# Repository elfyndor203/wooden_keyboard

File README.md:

# wooden_keyboard
My new keyboard

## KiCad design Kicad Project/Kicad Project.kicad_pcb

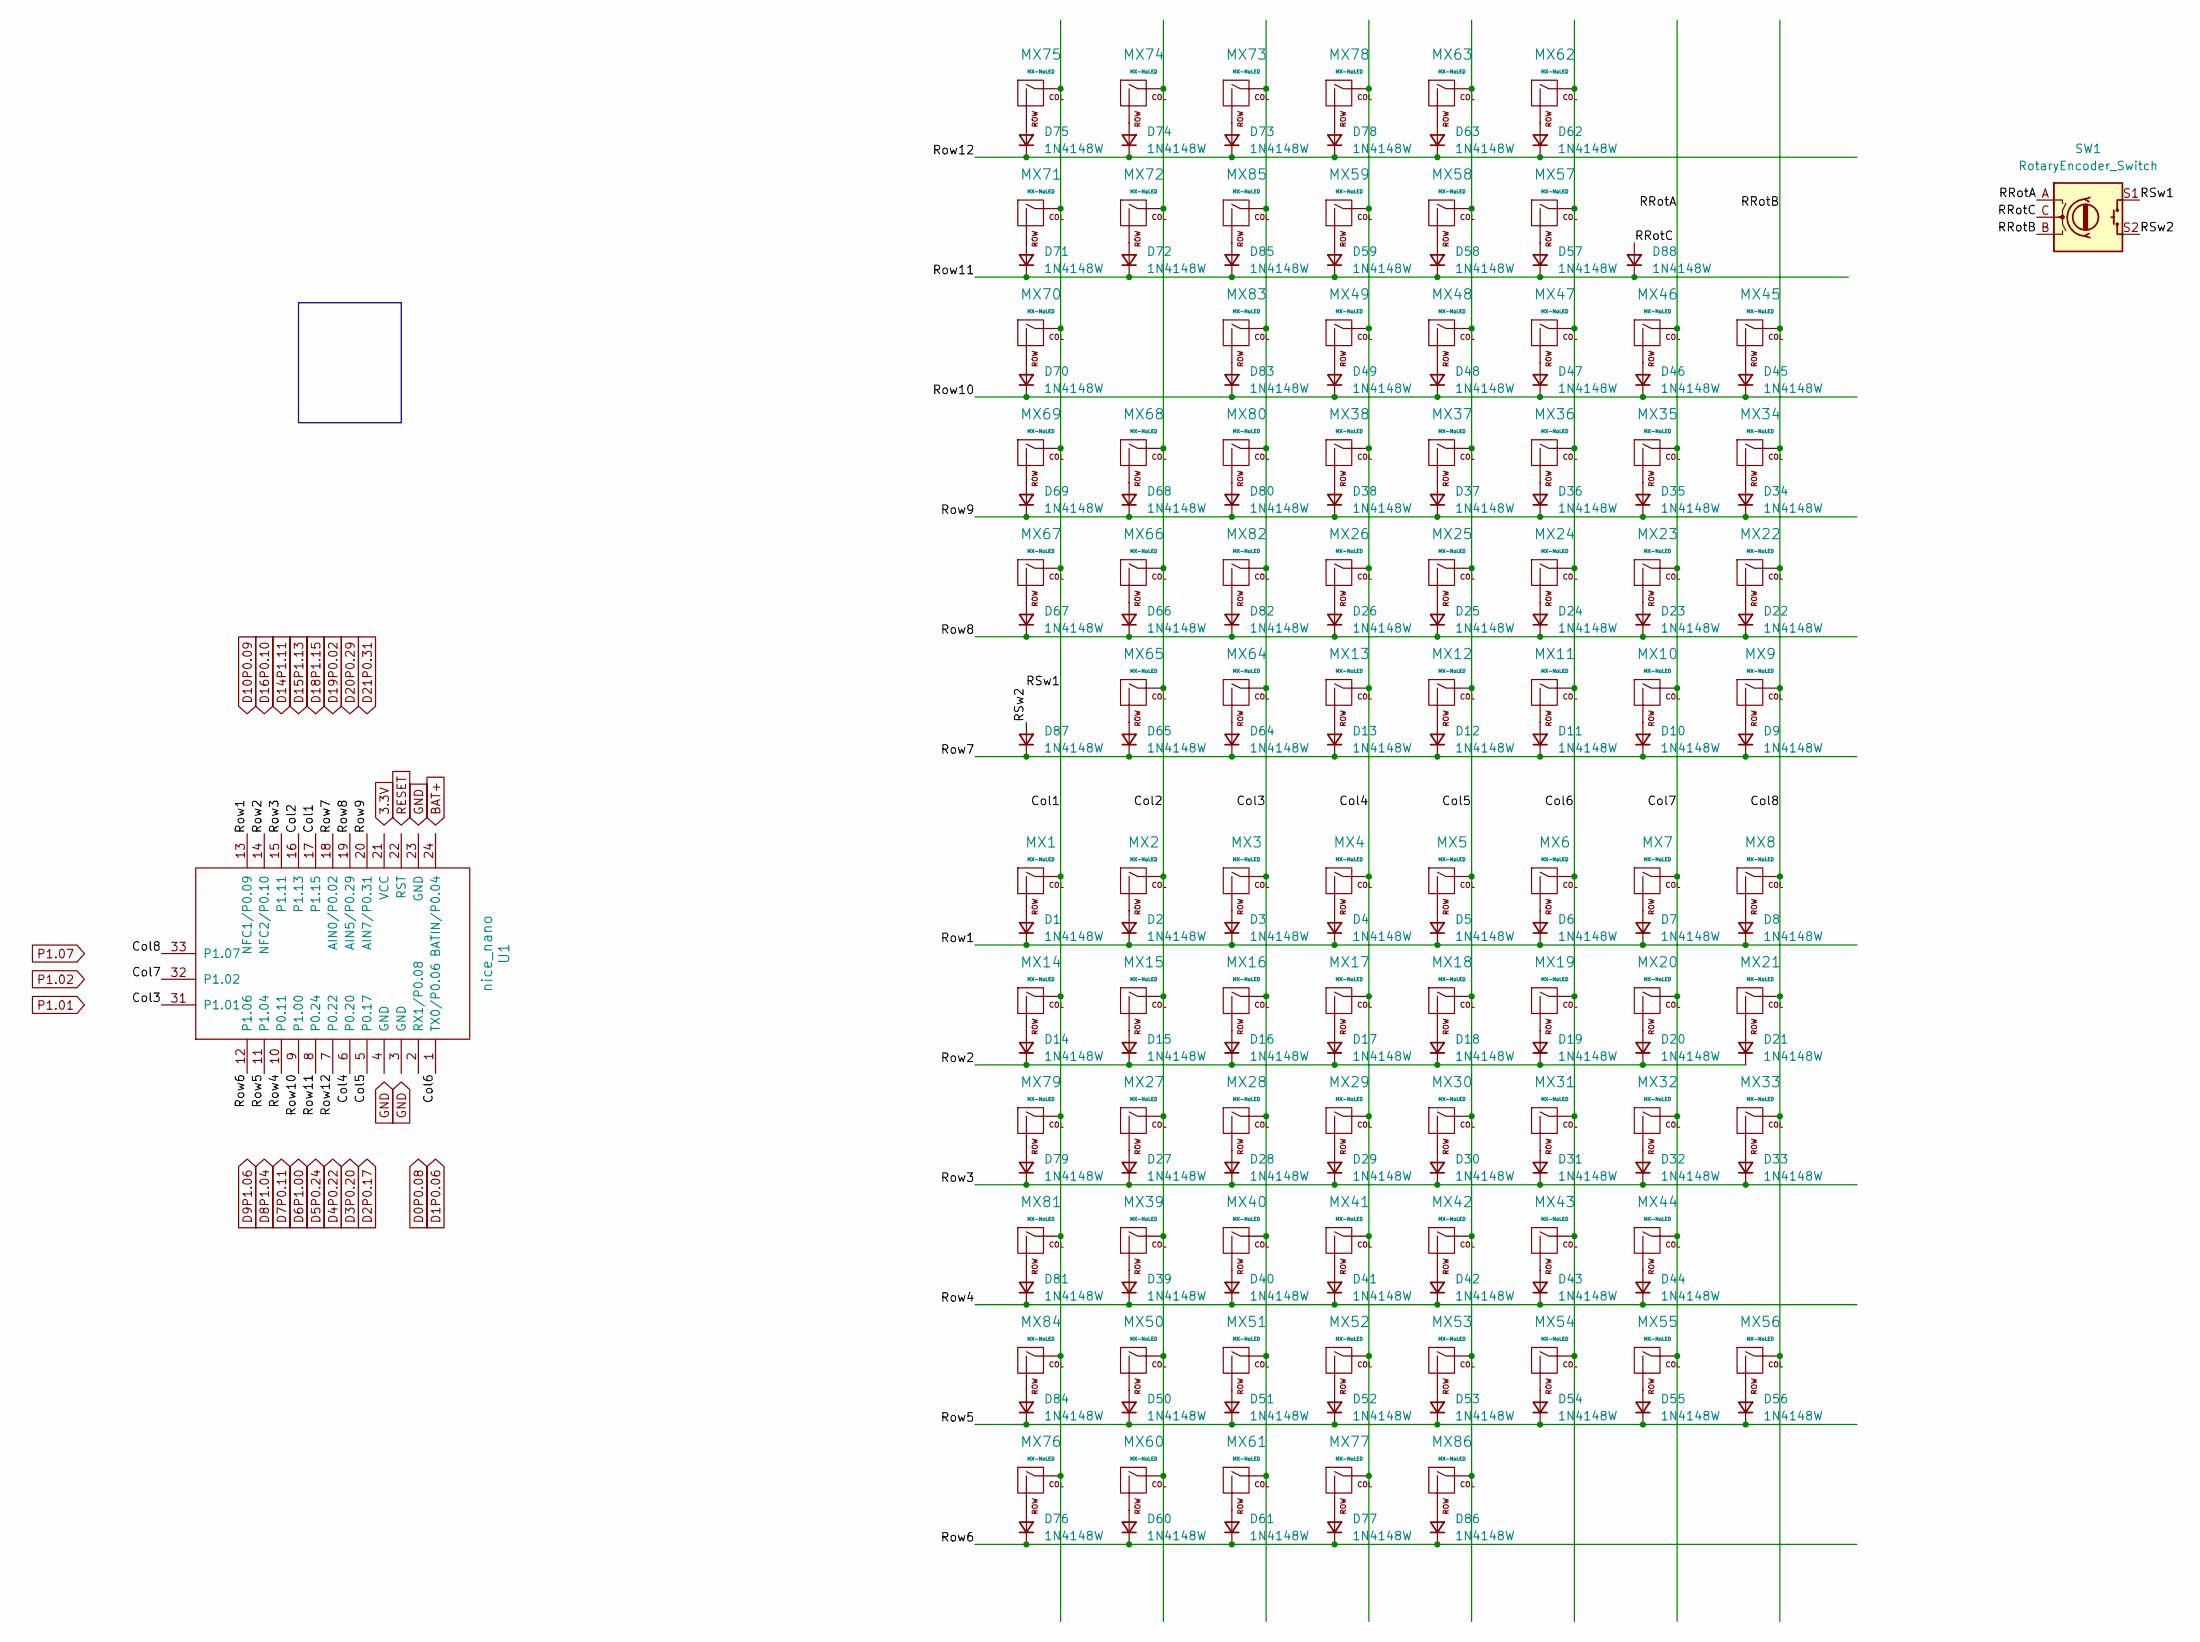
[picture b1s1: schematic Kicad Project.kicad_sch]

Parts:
D1, D2, D3, D4, D5, D6, D7, D8, D9, D10, D11, D12, D13, D14, D15, D16, D17, D18, D19, D20, D21, D22, D23, D24, D25, D26, D27, D28, D29, D30, D31, D32, D33, D34, D35, D36, D37, D38, D39, D40, D41, D42, D43, D44, D45, D46, D47, D48, D49, D50, D51, D52, D53, D54, D55, D56, D57, D58, D59, D60, D61, D62, D63, D64, D65, D66, D67, D68, D69, D70, D71, D72, D73, D74, D75, D76, D77, D78, D79, D80, D81, D82, D83, D84, D85, D86, D87, D88: 1N4148W; D_SOD-123
MX1, MX2, MX3, MX4, MX5, MX6, MX7, MX8, MX9, MX10, MX11, MX12, MX13, MX14, MX15, MX16, MX17, MX18, MX19, MX20, MX21, MX22, MX23, MX24, MX25, MX26, MX27, MX28, MX29, MX30, MX31, MX32, MX33, MX34, MX35, MX36, MX37, MX38, MX39, MX40, MX41, MX42, MX43, MX44, MX45, MX46, MX47, MX48, MX49, MX50, MX51, MX52, MX53, MX54, MX55, MX56, MX57, MX58, MX59, MX60, MX61, MX62, MX63, MX64, MX65, MX66, MX67, MX68, MX69, MX70, MX71, MX72, MX73, MX74, MX75: MX-NoLED; MXOnly-1U-Hotswap
MX76, MX77, MX78: MX-NoLED; MXOnly-1.25U-Hotswap
MX79, MX80: MX-NoLED; MXOnly-1.5U-Hotswap
MX81: MX-NoLED; MXOnly-1.75U-Hotswap
MX82: MX-NoLED; MXOnly-2U-Hotswap
MX83, MX84: MX-NoLED; MXOnly-2.25U-Hotswap
MX85: MX-NoLED; MXOnly-2.75U-Hotswap
MX86: MX-NoLED; MXOnly-6.25U-Hotswap
SW1: RotaryEncoder_Switch; RotaryEncoder_Alps_EC11E-Switch_Vertical_H20mm_MountingHoles
U1: nice_nano

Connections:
/Col1: MX1.1 (COL), MX14.1 (COL), MX67.1 (COL), MX69.1 (COL), MX70.1 (COL), MX71.1 (COL), MX75.1 (COL), MX76.1 (COL), MX79.1 (COL), MX81.1 (COL), MX84.1 (COL), SW1.S1, U1.17 (P1.15)
/Col2: MX2.1 (COL), MX15.1 (COL), MX27.1 (COL), MX39.1 (COL), MX50.1 (COL), MX60.1 (COL), MX65.1 (COL), MX66.1 (COL), MX68.1 (COL), MX72.1 (COL), MX74.1 (COL), U1.16 (P1.13)
/Col3: MX3.1 (COL), MX16.1 (COL), MX28.1 (COL), MX40.1 (COL), MX51.1 (COL), MX61.1 (COL), MX64.1 (COL), MX73.1 (COL), MX80.1 (COL), MX82.1 (COL), MX83.1 (COL), MX85.1 (COL), U1.31 (P1.01)
/Col4: MX4.1 (COL), MX13.1 (COL), MX17.1 (COL), MX26.1 (COL), MX29.1 (COL), MX38.1 (COL), MX41.1 (COL), MX49.1 (COL), MX52.1 (COL), MX59.1 (COL), MX77.1 (COL), MX78.1 (COL), U1.6 (P0.20)
/Col5: MX5.1 (COL), MX12.1 (COL), MX18.1 (COL), MX25.1 (COL), MX30.1 (COL), MX37.1 (COL), MX42.1 (COL), MX48.1 (COL), MX53.1 (COL), MX58.1 (COL), MX63.1 (COL), MX86.1 (COL), U1.5 (P0.17)
/Col6: MX6.1 (COL), MX11.1 (COL), MX19.1 (COL), MX24.1 (COL), MX31.1 (COL), MX36.1 (COL), MX43.1 (COL), MX47.1 (COL), MX54.1 (COL), MX57.1 (COL), MX62.1 (COL), U1.1 (TX0/P0.06)
/Col7: MX7.1 (COL), MX10.1 (COL), MX20.1 (COL), MX23.1 (COL), MX32.1 (COL), MX35.1 (COL), MX44.1 (COL), MX46.1 (COL), MX55.1 (COL), SW1.A, U1.32 (P1.02)
/Col8: MX8.1 (COL), MX9.1 (COL), MX21.1 (COL), MX22.1 (COL), MX33.1 (COL), MX34.1 (COL), MX45.1 (COL), MX56.1 (COL), SW1.B, U1.33 (P1.07)
/RRotC: D88.2 (A), SW1.C
/RSw2: D87.2 (A), SW1.S2
/Row1: D1.1 (K), D2.1 (K), D3.1 (K), D4.1 (K), D5.1 (K), D6.1 (K), D7.1 (K), D8.1 (K), U1.13 (NFC1/P0.09)
/Row2: D14.1 (K), D15.1 (K), D16.1 (K), D17.1 (K), D18.1 (K), D19.1 (K), D20.1 (K), D21.1 (K), U1.14 (NFC2/P0.10)
/Row3: D27.1 (K), D28.1 (K), D29.1 (K), D30.1 (K), D31.1 (K), D32.1 (K), D33.1 (K), D79.1 (K), U1.15 (P1.11)
/Row4: D39.1 (K), D40.1 (K), D41.1 (K), D42.1 (K), D43.1 (K), D44.1 (K), D81.1 (K), U1.10 (P0.11)
/Row5: D50.1 (K), D51.1 (K), D52.1 (K), D53.1 (K), D54.1 (K), D55.1 (K), D56.1 (K), D84.1 (K), U1.11 (P1.04)
/Row6: D60.1 (K), D61.1 (K), D76.1 (K), D77.1 (K), D86.1 (K), U1.12 (P1.06)
/Row7: D9.1 (K), D10.1 (K), D11.1 (K), D12.1 (K), D13.1 (K), D64.1 (K), D65.1 (K), D87.1 (K), U1.18 (AIN0/P0.02)
/Row8: D22.1 (K), D23.1 (K), D24.1 (K), D25.1 (K), D26.1 (K), D66.1 (K), D67.1 (K), D82.1 (K), U1.19 (AIN5/P0.29)
/Row9: D34.1 (K), D35.1 (K), D36.1 (K), D37.1 (K), D38.1 (K), D68.1 (K), D69.1 (K), D80.1 (K), U1.20 (AIN7/P0.31)
/Row10: D45.1 (K), D46.1 (K), D47.1 (K), D48.1 (K), D49.1 (K), D70.1 (K), D83.1 (K), U1.9 (P1.00)
/Row11: D57.1 (K), D58.1 (K), D59.1 (K), D71.1 (K), D72.1 (K), D85.1 (K), D88.1 (K), U1.8 (P0.24)
/Row12: D62.1 (K), D63.1 (K), D73.1 (K), D74.1 (K), D75.1 (K), D78.1 (K), U1.7 (P0.22)
unnamed: D1.2 (A), MX1.2 (ROW)
unnamed: D2.2 (A), MX2.2 (ROW)
unnamed: D3.2 (A), MX3.2 (ROW)
unnamed: D4.2 (A), MX4.2 (ROW)
unnamed: D5.2 (A), MX5.2 (ROW)
unnamed: D6.2 (A), MX6.2 (ROW)
unnamed: D7.2 (A), MX7.2 (ROW)
unnamed: D8.2 (A), MX8.2 (ROW)
unnamed: D9.2 (A), MX9.2 (ROW)
unnamed: D10.2 (A), MX10.2 (ROW)
unnamed: D11.2 (A), MX11.2 (ROW)
unnamed: D12.2 (A), MX12.2 (ROW)
unnamed: D13.2 (A), MX13.2 (ROW)
unnamed: D14.2 (A), MX14.2 (ROW)
unnamed: D15.2 (A), MX15.2 (ROW)
unnamed: D16.2 (A), MX16.2 (ROW)
unnamed: D17.2 (A), MX17.2 (ROW)
unnamed: D18.2 (A), MX18.2 (ROW)
unnamed: D19.2 (A), MX19.2 (ROW)
unnamed: D20.2 (A), MX20.2 (ROW)
unnamed: D21.2 (A), MX21.2 (ROW)
unnamed: D22.2 (A), MX22.2 (ROW)
unnamed: D23.2 (A), MX23.2 (ROW)
unnamed: D24.2 (A), MX24.2 (ROW)
unnamed: D25.2 (A), MX25.2 (ROW)
unnamed: D26.2 (A), MX26.2 (ROW)
unnamed: D27.2 (A), MX27.2 (ROW)
unnamed: D28.2 (A), MX28.2 (ROW)
unnamed: D29.2 (A), MX29.2 (ROW)
unnamed: D30.2 (A), MX30.2 (ROW)
unnamed: D31.2 (A), MX31.2 (ROW)
unnamed: D32.2 (A), MX32.2 (ROW)
unnamed: D33.2 (A), MX33.2 (ROW)
unnamed: D34.2 (A), MX34.2 (ROW)
unnamed: D35.2 (A), MX35.2 (ROW)
unnamed: D36.2 (A), MX36.2 (ROW)
unnamed: D37.2 (A), MX37.2 (ROW)
unnamed: D38.2 (A), MX38.2 (ROW)
unnamed: D39.2 (A), MX39.2 (ROW)
unnamed: D40.2 (A), MX40.2 (ROW)
unnamed: D41.2 (A), MX41.2 (ROW)
unnamed: D42.2 (A), MX42.2 (ROW)
unnamed: D43.2 (A), MX43.2 (ROW)
unnamed: D44.2 (A), MX44.2 (ROW)
unnamed: D45.2 (A), MX45.2 (ROW)
unnamed: D46.2 (A), MX46.2 (ROW)
unnamed: D47.2 (A), MX47.2 (ROW)
unnamed: D48.2 (A), MX48.2 (ROW)
unnamed: D49.2 (A), MX49.2 (ROW)
unnamed: D50.2 (A), MX50.2 (ROW)
unnamed: D51.2 (A), MX51.2 (ROW)
unnamed: D52.2 (A), MX52.2 (ROW)
unnamed: D53.2 (A), MX53.2 (ROW)
unnamed: D54.2 (A), MX54.2 (ROW)
unnamed: D55.2 (A), MX55.2 (ROW)
unnamed: D56.2 (A), MX56.2 (ROW)
unnamed: D57.2 (A), MX57.2 (ROW)
unnamed: D58.2 (A), MX58.2 (ROW)
unnamed: D59.2 (A), MX59.2 (ROW)
unnamed: D60.2 (A), MX60.2 (ROW)
unnamed: D61.2 (A), MX61.2 (ROW)
unnamed: D62.2 (A), MX62.2 (ROW)
unnamed: D63.2 (A), MX63.2 (ROW)
unnamed: D64.2 (A), MX64.2 (ROW)
unnamed: D65.2 (A), MX65.2 (ROW)
unnamed: D66.2 (A), MX66.2 (ROW)
unnamed: D67.2 (A), MX67.2 (ROW)
unnamed: D68.2 (A), MX68.2 (ROW)
unnamed: D69.2 (A), MX69.2 (ROW)
unnamed: D70.2 (A), MX70.2 (ROW)
unnamed: D71.2 (A), MX71.2 (ROW)
unnamed: D72.2 (A), MX72.2 (ROW)
unnamed: D73.2 (A), MX73.2 (ROW)
unnamed: D74.2 (A), MX74.2 (ROW)
unnamed: D75.2 (A), MX75.2 (ROW)
unnamed: D76.2 (A), MX76.2 (ROW)
unnamed: D77.2 (A), MX77.2 (ROW)
unnamed: D78.2 (A), MX78.2 (ROW)
unnamed: D79.2 (A), MX79.2 (ROW)
unnamed: D80.2 (A), MX80.2 (ROW)
unnamed: D81.2 (A), MX81.2 (ROW)
unnamed: D82.2 (A), MX82.2 (ROW)
unnamed: D83.2 (A), MX83.2 (ROW)
unnamed: D84.2 (A), MX84.2 (ROW)
unnamed: D85.2 (A), MX85.2 (ROW)
unnamed: D86.2 (A), MX86.2 (ROW)

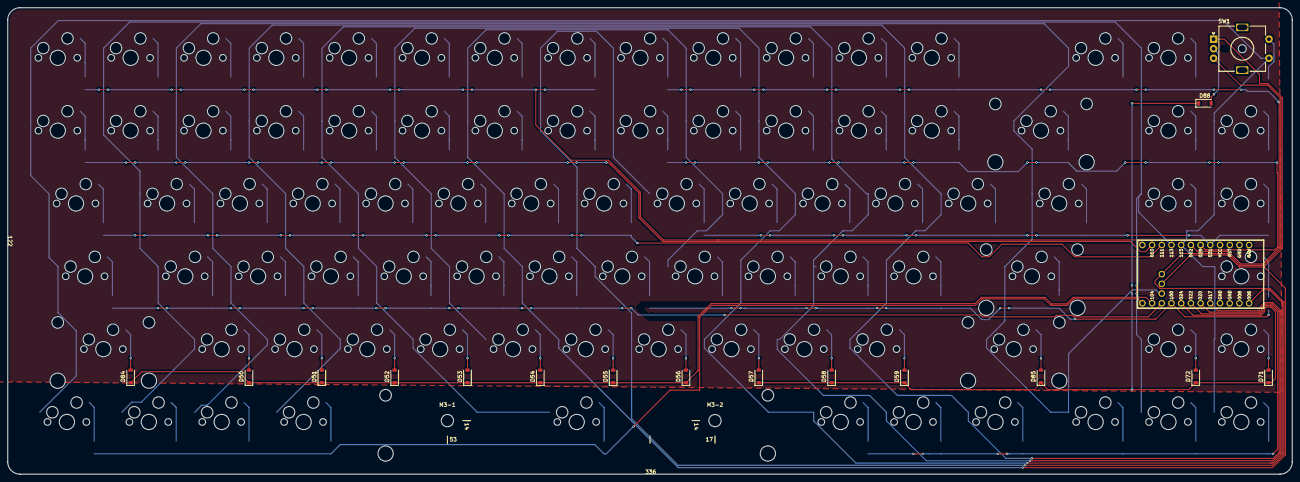
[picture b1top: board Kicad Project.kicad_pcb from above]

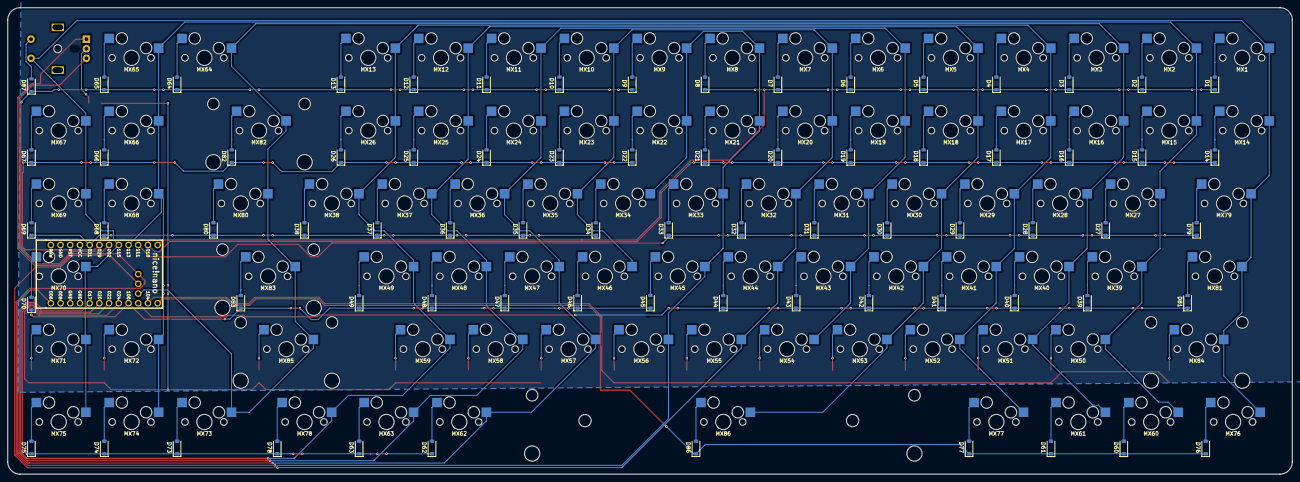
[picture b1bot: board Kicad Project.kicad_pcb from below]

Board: 2 copper layers, 336.0 x 122.0 mm, 178 parts (74 on the bottom side), 108 nets.

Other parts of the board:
M3-1, M3-2: MountingHole_3.2mm_M3

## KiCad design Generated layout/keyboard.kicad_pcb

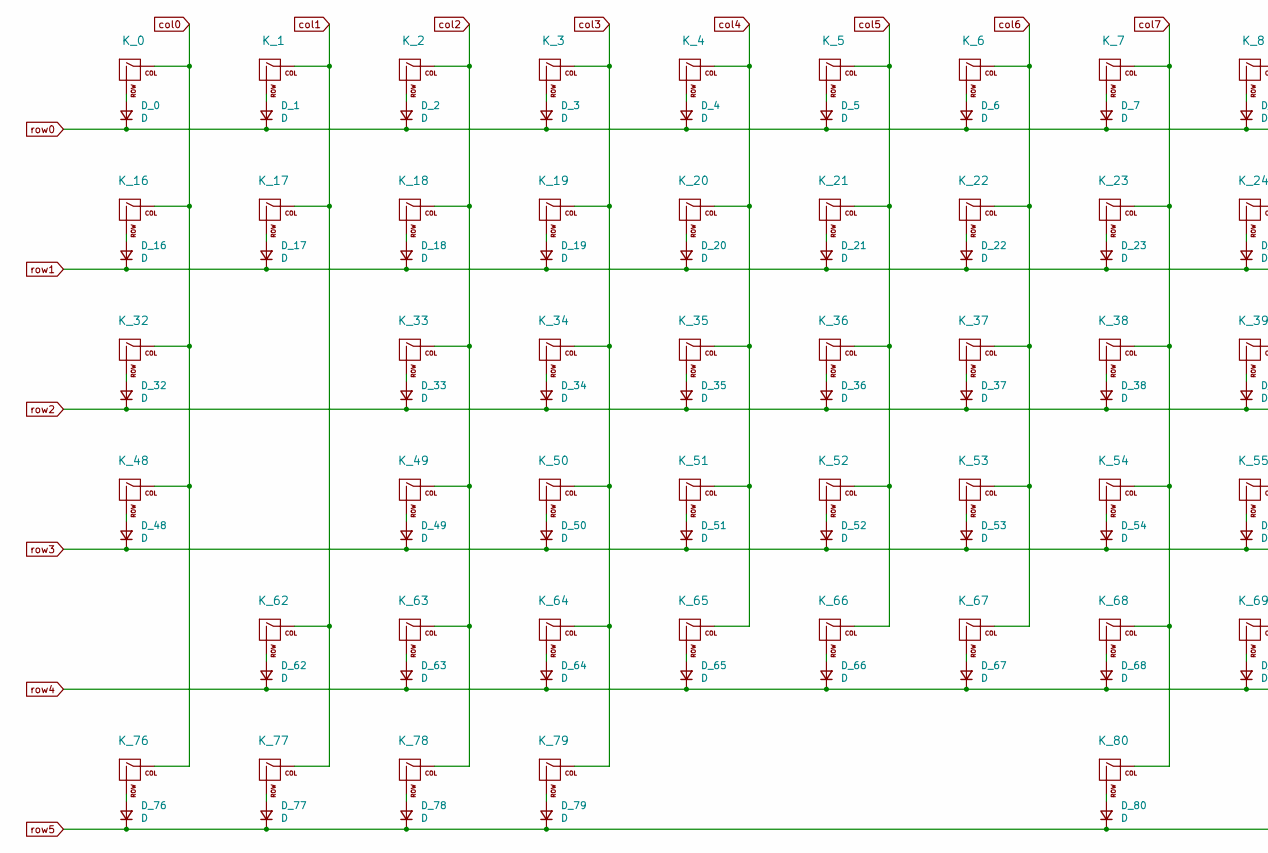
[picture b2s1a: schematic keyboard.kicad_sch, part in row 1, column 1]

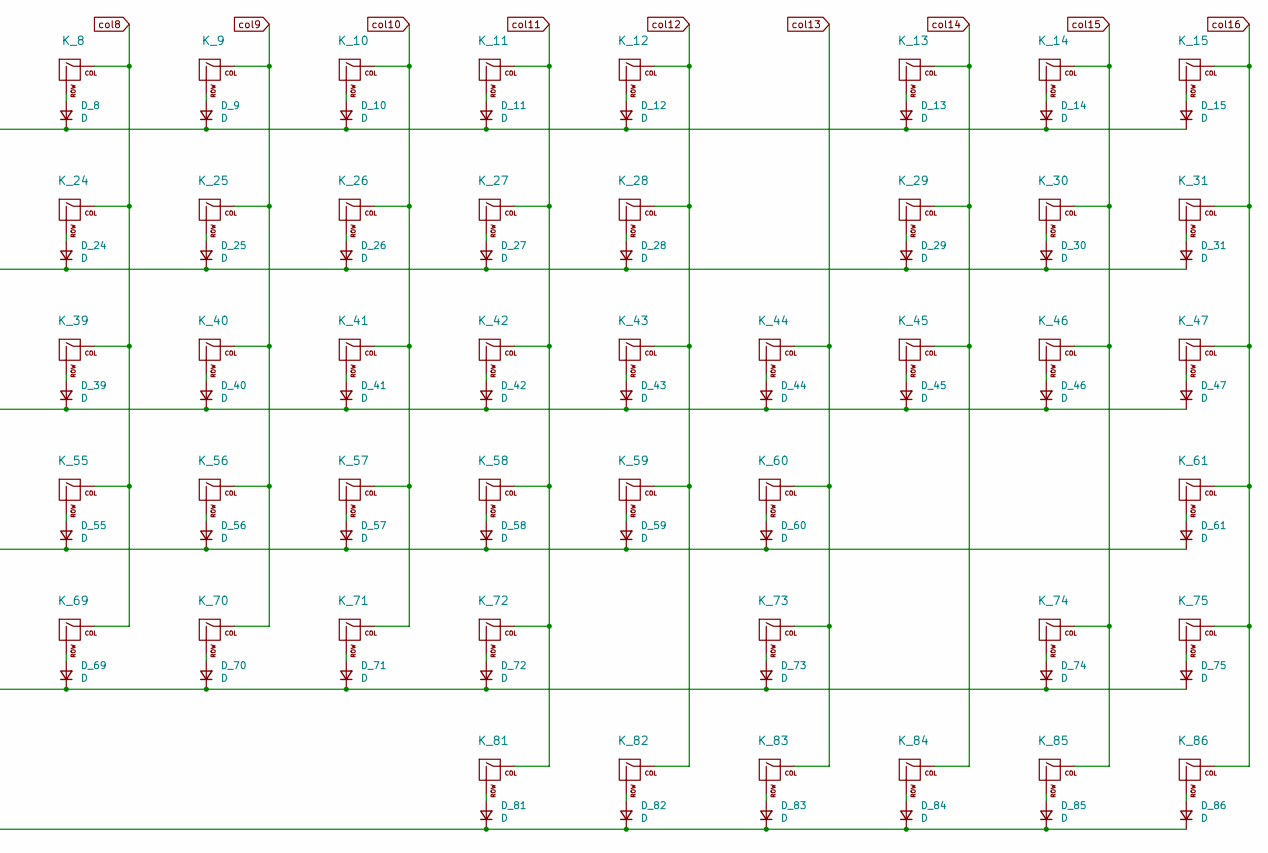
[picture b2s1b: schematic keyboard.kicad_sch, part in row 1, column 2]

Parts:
D_0, D_1, D_2, D_3, D_4, D_5, D_6, D_7, D_8, D_9, D_10, D_11, D_12, D_13, D_14, D_15, D_16, D_17, D_18, D_19, D_20, D_21, D_22, D_23, D_24, D_25, D_26, D_27, D_28, D_29, D_30, D_31, D_32, D_33, D_34, D_35, D_36, D_37, D_38, D_39, D_40, D_41, D_42, D_43, D_44, D_45, D_46, D_47, D_48, D_49, D_50, D_51, D_52, D_53, D_54, D_55, D_56, D_57, D_58, D_59, D_60, D_61, D_62, D_63, D_64, D_65, D_66, D_67, D_68, D_69, D_70, D_71, D_72, D_73, D_74, D_75, D_76, D_77, D_78, D_79, D_80, D_81, D_82, D_83, D_84, D_85, D_86: D; D_SOD-123
K_0, K_1, K_2, K_3, K_4, K_5, K_6, K_7, K_8, K_9, K_10, K_11, K_12, K_13, K_14, K_15, K_16, K_17, K_18, K_19, K_20, K_21, K_22, K_23, K_24, K_25, K_26, K_27, K_28, K_30, K_31, K_33, K_34, K_35, K_36, K_37, K_38, K_39, K_40, K_41, K_42, K_43, K_44, K_46, K_47, K_49, K_50, K_51, K_52, K_53, K_54, K_55, K_56, K_57, K_58, K_59, K_61, K_63, K_64, K_65, K_66, K_67, K_68, K_69, K_70, K_71, K_72, K_74, K_75, K_77, K_78, K_81, K_82, K_84, K_85, K_86: KEYSW; MX-1U-NoLED
K_29: KEYSW; MX-2U-NoLED
K_32, K_45: KEYSW; MX-1.5U-NoLED
K_48: KEYSW; MX-1.75U-NoLED
K_60, K_62: KEYSW; MX-2.25U-NoLED
K_73: KEYSW; MX-2.75U-NoLED
K_76, K_79, K_83: KEYSW; MX-1.25U-NoLED
K_80: KEYSW; MX-6.25U-NoLED

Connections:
unnamed: D_0.2 (A), K_0.2 (ROW)
unnamed: D_1.2 (A), K_1.2 (ROW)
unnamed: D_2.2 (A), K_2.2 (ROW)
unnamed: D_3.2 (A), K_3.2 (ROW)
unnamed: D_4.2 (A), K_4.2 (ROW)
unnamed: D_5.2 (A), K_5.2 (ROW)
unnamed: D_6.2 (A), K_6.2 (ROW)
unnamed: D_7.2 (A), K_7.2 (ROW)
unnamed: D_8.2 (A), K_8.2 (ROW)
unnamed: D_9.2 (A), K_9.2 (ROW)
unnamed: D_10.2 (A), K_10.2 (ROW)
unnamed: D_11.2 (A), K_11.2 (ROW)
unnamed: D_12.2 (A), K_12.2 (ROW)
unnamed: D_13.2 (A), K_13.2 (ROW)
unnamed: D_14.2 (A), K_14.2 (ROW)
unnamed: D_15.2 (A), K_15.2 (ROW)
unnamed: D_16.2 (A), K_16.2 (ROW)
unnamed: D_17.2 (A), K_17.2 (ROW)
unnamed: D_18.2 (A), K_18.2 (ROW)
unnamed: D_19.2 (A), K_19.2 (ROW)
unnamed: D_20.2 (A), K_20.2 (ROW)
unnamed: D_21.2 (A), K_21.2 (ROW)
unnamed: D_22.2 (A), K_22.2 (ROW)
unnamed: D_23.2 (A), K_23.2 (ROW)
unnamed: D_24.2 (A), K_24.2 (ROW)
unnamed: D_25.2 (A), K_25.2 (ROW)
unnamed: D_26.2 (A), K_26.2 (ROW)
unnamed: D_27.2 (A), K_27.2 (ROW)
unnamed: D_28.2 (A), K_28.2 (ROW)
unnamed: D_29.2 (A), K_29.2 (ROW)
unnamed: D_30.2 (A), K_30.2 (ROW)
unnamed: D_31.2 (A), K_31.2 (ROW)
unnamed: D_32.2 (A), K_32.2 (ROW)
unnamed: D_33.2 (A), K_33.2 (ROW)
unnamed: D_34.2 (A), K_34.2 (ROW)
unnamed: D_35.2 (A), K_35.2 (ROW)
unnamed: D_36.2 (A), K_36.2 (ROW)
unnamed: D_37.2 (A), K_37.2 (ROW)
unnamed: D_38.2 (A), K_38.2 (ROW)
unnamed: D_39.2 (A), K_39.2 (ROW)
unnamed: D_40.2 (A), K_40.2 (ROW)
unnamed: D_41.2 (A), K_41.2 (ROW)
unnamed: D_42.2 (A), K_42.2 (ROW)
unnamed: D_43.2 (A), K_43.2 (ROW)
unnamed: D_44.2 (A), K_44.2 (ROW)
unnamed: D_45.2 (A), K_45.2 (ROW)
unnamed: D_46.2 (A), K_46.2 (ROW)
unnamed: D_47.2 (A), K_47.2 (ROW)
unnamed: D_48.2 (A), K_48.2 (ROW)
unnamed: D_49.2 (A), K_49.2 (ROW)
unnamed: D_50.2 (A), K_50.2 (ROW)
unnamed: D_51.2 (A), K_51.2 (ROW)
unnamed: D_52.2 (A), K_52.2 (ROW)
unnamed: D_53.2 (A), K_53.2 (ROW)
unnamed: D_54.2 (A), K_54.2 (ROW)
unnamed: D_55.2 (A), K_55.2 (ROW)
unnamed: D_56.2 (A), K_56.2 (ROW)
unnamed: D_57.2 (A), K_57.2 (ROW)
unnamed: D_58.2 (A), K_58.2 (ROW)
unnamed: D_59.2 (A), K_59.2 (ROW)
unnamed: D_60.2 (A), K_60.2 (ROW)
unnamed: D_61.2 (A), K_61.2 (ROW)
unnamed: D_62.2 (A), K_62.2 (ROW)
unnamed: D_63.2 (A), K_63.2 (ROW)
unnamed: D_64.2 (A), K_64.2 (ROW)
unnamed: D_65.2 (A), K_65.2 (ROW)
unnamed: D_66.2 (A), K_66.2 (ROW)
unnamed: D_67.2 (A), K_67.2 (ROW)
unnamed: D_68.2 (A), K_68.2 (ROW)
unnamed: D_69.2 (A), K_69.2 (ROW)
unnamed: D_70.2 (A), K_70.2 (ROW)
unnamed: D_71.2 (A), K_71.2 (ROW)
unnamed: D_72.2 (A), K_72.2 (ROW)
unnamed: D_73.2 (A), K_73.2 (ROW)
unnamed: D_74.2 (A), K_74.2 (ROW)
unnamed: D_75.2 (A), K_75.2 (ROW)
unnamed: D_76.2 (A), K_76.2 (ROW)
unnamed: D_77.2 (A), K_77.2 (ROW)
unnamed: D_78.2 (A), K_78.2 (ROW)
unnamed: D_79.2 (A), K_79.2 (ROW)
unnamed: D_80.2 (A), K_80.2 (ROW)
unnamed: D_81.2 (A), K_81.2 (ROW)
unnamed: D_82.2 (A), K_82.2 (ROW)
unnamed: D_83.2 (A), K_83.2 (ROW)
unnamed: D_84.2 (A), K_84.2 (ROW)
unnamed: D_85.2 (A), K_85.2 (ROW)
unnamed: D_86.2 (A), K_86.2 (ROW)
col0: K_0.1 (COL), K_16.1 (COL), K_32.1 (COL), K_48.1 (COL), K_76.1 (COL)
col1: K_1.1 (COL), K_17.1 (COL), K_62.1 (COL), K_77.1 (COL)
col2: K_2.1 (COL), K_18.1 (COL), K_33.1 (COL), K_49.1 (COL), K_63.1 (COL), K_78.1 (COL)
col3: K_3.1 (COL), K_19.1 (COL), K_34.1 (COL), K_50.1 (COL), K_64.1 (COL), K_79.1 (COL)
col4: K_4.1 (COL), K_20.1 (COL), K_35.1 (COL), K_51.1 (COL), K_65.1 (COL)
col5: K_5.1 (COL), K_21.1 (COL), K_36.1 (COL), K_52.1 (COL), K_66.1 (COL)
col6: K_6.1 (COL), K_22.1 (COL), K_37.1 (COL), K_53.1 (COL), K_67.1 (COL)
col7: K_7.1 (COL), K_23.1 (COL), K_38.1 (COL), K_54.1 (COL), K_68.1 (COL), K_80.1 (COL)
col8: K_8.1 (COL), K_24.1 (COL), K_39.1 (COL), K_55.1 (COL), K_69.1 (COL)
col9: K_9.1 (COL), K_25.1 (COL), K_40.1 (COL), K_56.1 (COL), K_70.1 (COL)
col10: K_10.1 (COL), K_26.1 (COL), K_41.1 (COL), K_57.1 (COL), K_71.1 (COL)
col11: K_11.1 (COL), K_27.1 (COL), K_42.1 (COL), K_58.1 (COL), K_72.1 (COL), K_81.1 (COL)
col12: K_12.1 (COL), K_28.1 (COL), K_43.1 (COL), K_59.1 (COL), K_82.1 (COL)
col13: K_44.1 (COL), K_60.1 (COL), K_73.1 (COL), K_83.1 (COL)
col14: K_13.1 (COL), K_29.1 (COL), K_45.1 (COL), K_84.1 (COL)
col15: K_14.1 (COL), K_30.1 (COL), K_46.1 (COL), K_74.1 (COL), K_85.1 (COL)
col16: K_15.1 (COL), K_31.1 (COL), K_47.1 (COL), K_61.1 (COL), K_75.1 (COL), K_86.1 (COL)
row0: D_0.1 (K), D_1.1 (K), D_2.1 (K), D_3.1 (K), D_4.1 (K), D_5.1 (K), D_6.1 (K), D_7.1 (K), D_8.1 (K), D_9.1 (K), D_10.1 (K), D_11.1 (K), D_12.1 (K), D_13.1 (K), D_14.1 (K), D_15.1 (K)
row1: D_16.1 (K), D_17.1 (K), D_18.1 (K), D_19.1 (K), D_20.1 (K), D_21.1 (K), D_22.1 (K), D_23.1 (K), D_24.1 (K), D_25.1 (K), D_26.1 (K), D_27.1 (K), D_28.1 (K), D_29.1 (K), D_30.1 (K), D_31.1 (K)
row2: D_32.1 (K), D_33.1 (K), D_34.1 (K), D_35.1 (K), D_36.1 (K), D_37.1 (K), D_38.1 (K), D_39.1 (K), D_40.1 (K), D_41.1 (K), D_42.1 (K), D_43.1 (K), D_44.1 (K), D_45.1 (K), D_46.1 (K), D_47.1 (K)
row3: D_48.1 (K), D_49.1 (K), D_50.1 (K), D_51.1 (K), D_52.1 (K), D_53.1 (K), D_54.1 (K), D_55.1 (K), D_56.1 (K), D_57.1 (K), D_58.1 (K), D_59.1 (K), D_60.1 (K), D_61.1 (K)
row4: D_62.1 (K), D_63.1 (K), D_64.1 (K), D_65.1 (K), D_66.1 (K), D_67.1 (K), D_68.1 (K), D_69.1 (K), D_70.1 (K), D_71.1 (K), D_72.1 (K), D_73.1 (K), D_74.1 (K), D_75.1 (K)
row5: D_76.1 (K), D_77.1 (K), D_78.1 (K), D_79.1 (K), D_80.1 (K), D_81.1 (K), D_82.1 (K), D_83.1 (K), D_84.1 (K), D_85.1 (K), D_86.1 (K)

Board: 2 copper layers, 174 parts (87 on the bottom side), 110 nets, no tracks yet.

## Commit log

2025-06-27 add local
2025-06-29 schematic inital version no rot
2025-06-29 routed minus rot and controller
2025-06-29 fully routed draft
2025-07-03 most diodes rerouted to back
2025-07-13 stable before rewire
2025-07-20 pcbs ordered july 13th 2025
2025-07-20 add zmk submodule
2025-07-20 rename submodule
2025-07-22 downloaded zmk, zephyr, have to build zephyr to get .h files
2025-08-07 firmwaregit add .
2025-08-15 WORKING FIRMWARE
2025-09-15 upload current fusion file
